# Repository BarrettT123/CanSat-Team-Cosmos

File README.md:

(The software I contributed to this project can be found in the CanSat-Team-Cosmos-Software repository)

Cansat Competition Description:
- The Cansat competition is a design-build-fly competition that provides teams with an
opportunity to experience the design life-cycle of an aerospace system. The Cansat
competition is designed to reflect a typical aerospace program on a small scale and includes
all aspects of an aerospace program from the preliminary design review to post flight review.
The mission and its requirements are designed to reflect various aspects of real world
missions including telemetry, communications, and autonomous operations. Each team is
scored throughout the competition on real-world deliverables such as schedules, design
review presentations, and demonstration flights.

Mission Overview:
- Design a Cansat that consists of a payload and a container that mounts on top of the rocket.
The payload rests inside the container at launch and includes the nose cone as part of the
payload.
- The container with the payload shall deploy from the rocket when the rocket reaches peak
altitude and the rocket motor ejection forces a separation. The container with the payload
shall descend at a rate of no more than 20 meters/second using a parachute that
automatically deploys at separation.
- At 75% peak altitude, the payload shall separate from the container and descend using an
auto-gyro descent control system until landing. The descent rate shall be 5 meters/second.
- A video camera shall show the separation of the payload from the container and the auto-gyro
functioning. A second video camera shall be pointing downward at 45 degrees from nadir
and oriented north during descent and be spin stabilized so that the view of the earth is not
rotating.
- The Cansat shall collect sensor data during ascent and descent and transmit the data to a
ground station at a 1 Hz rate. The sensor data shall include interior temperature, battery
voltage, altitude, auto-gyro rotation rate, acceleration, rate, magnetic field, and GPS position.

Post-Flight Cansat Payload:

Ground Station during Landing:

Software Contributors:
- `GCS`:
  - Diego Romero-Cardona

- `FSW`:
  - Caleb Wiley
  - Akhil Samiraju
  - Barrett Twining
  - Diego Romero-Cardona

- `PID Board`:
  - Caleb Wiley
  - Barrett Twining
  - Luke Wiggins

Competition Flight Data:
|TEAM_ID|MISSION_TIME|PACKET_COUNT|MODE|STATE        |ALTITUDE|TEMPERATURE|PRESSURE|VOLTAGE|GYRO_R |GYRO_P |GYRO_Y  |ACCEL_R|ACCEL_P|ACCEL_Y|MAG_R|MAG_P|MAG_Y|AUTO_GYRO_ROTATION_RATE|GPS_TIME|GPS_ALTITUDE|GPS_LATITUDE|GPS_LONGITUDE|GPS_SATS|CMD_ECHO   |TEAM_NAME|
|-------|------------|------------|----|-------------|--------|-----------|--------|-------|-------|-------|--------|-------|-------|-------|-----|-----|-----|-----------------------|--------|------------|------------|-------------|--------|-----------|---------|
|3195   |18:26:32    |972         |F   |LAUNCH_PAD   |-0.9    |40.6       |915.5   |7.9    |-0.79  |-1.28  |0.24    |-0.02  |0.00   |-0.49  |-42.6|-3.0 |61.6 |0                      |00:00:00|0.0         |0.00000     |0.00000      |0       |ST_UTC_TIME|COSMOS   |
|3195   |18:26:33    |973         |F   |LAUNCH_PAD   |-0.9    |40.7       |915.5   |7.9    |-0.67  |-0.98  |0.37    |-0.02  |-0.00  |-0.49  |-43.5|-2.9 |59.0 |0                      |00:00:00|0.0         |0.00000     |0.00000      |0       |ST_UTC_TIME|COSMOS   |
|3195   |18:26:38    |978         |F   |ASCENT       |186.3   |40.7       |895.4   |7.9    |-10.68 |7.63   |-123.54 |-0.10  |-0.05  |-4.00  |-45.7|-7.9 |61.9 |0                      |00:00:00|0.0         |0.00000     |0.00000      |0       |ST_UTC_TIME|COSMOS   |
|3195   |18:26:39    |979         |F   |ASCENT       |455.9   |40.6       |867.0   |7.9    |24.29  |-9.09  |-300.78 |-0.12  |0.09   |0.64   |-37.9|-2.8 |63.8 |0                      |00:00:00|0.0         |0.00000     |0.00000      |0       |ST_UTC_TIME|COSMOS   |
|3195   |18:26:40    |980         |F   |ASCENT       |478.8   |40.6       |864.7   |7.9    |3.36   |-19.84 |-251.46 |-0.04  |0.14   |0.51   |-33.1|-3.6 |62.0 |0                      |00:00:00|0.0         |0.00000     |0.00000      |0       |ST_UTC_TIME|COSMOS   |
|3195   |18:26:41    |981         |F   |APOGEE       |500.4   |40.6       |862.4   |7.9    |-1.53  |-13.43 |-183.53 |0.01   |0.15   |0.31   |-6.4 |-20.7|62.3 |0                      |00:00:00|0.0         |0.00000     |0.00000      |0       |ST_UTC_TIME|COSMOS   |
|3195   |18:26:42    |982         |F   |APOGEE       |530.2   |40.5       |859.3   |7.9    |8.67   |-17.94 |-138.37 |-0.02  |0.10   |0.20   |-46.8|-33.5|58.3 |0                      |00:00:00|0.0         |0.00000     |0.00000      |0       |ST_UTC_TIME|COSMOS   |
|3195   |18:26:43    |983         |F   |APOGEE       |557.5   |40.5       |856.5   |7.9    |5.19   |-14.28 |-94.97  |-0.02  |0.06   |0.12   |-5.4 |-31.5|58.2 |0                      |00:00:00|0.0         |0.00000     |0.00000      |0       |ST_UTC_TIME|COSMOS   |
|3195   |18:26:44    |984         |F   |APOGEE       |579.7   |40.5       |854.3   |7.9    |4.88   |-12.02 |-74.28  |-0.00  |0.03   |0.07   |-32.1|-4.0 |63.1 |0                      |00:00:00|0.0         |0.00000     |0.00000      |0       |ST_UTC_TIME|COSMOS   |
|3195   |18:26:45    |985         |F   |APOGEE       |597.4   |40.5       |852.4   |7.9    |1.59   |-8.97  |-56.64  |-0.00  |0.01   |0.03   |-49.3|-27.0|60.7 |0                      |00:00:00|0.0         |0.00000     |0.00000      |0       |ST_UTC_TIME|COSMOS   |
|3195   |18:26:46    |986         |F   |APOGEE       |611.3   |40.6       |851.0   |7.9    |-27.71 |-4.70  |-52.43  |-0.00  |-0.03  |0.05   |-36.9|-36.6|62.3 |0                      |00:00:00|0.0         |0.00000     |0.00000      |0       |ST_UTC_TIME|COSMOS   |
|3195   |18:26:47    |987         |F   |APOGEE       |616.2   |40.6       |850.5   |7.9    |23.19  |31.19  |-55.60  |0.01   |-0.02  |0.02   |-15.8|-34.8|61.7 |0                      |00:00:00|0.0         |0.00000     |0.00000      |0       |ST_UTC_TIME|COSMOS   |
|3195   |18:26:48    |988         |F   |DESCENT      |612.7   |40.6       |850.9   |7.9    |-62.93 |243.71 |-11.78  |0.20   |0.02   |-0.08  |9.2  |-9.7 |-12.0|0                      |00:00:00|0.0         |0.00000     |0.00000      |0       |ST_UTC_TIME|COSMOS   |
|3195   |18:26:49    |989         |F   |DESCENT      |603.2   |40.6       |851.9   |7.9    |-166.63|83.56  |115.36  |0.48   |-0.20  |0.09   |3.3  |-28.4|-22.3|0                      |00:00:00|0.0         |0.00000     |0.00000      |0       |ST_UTC_TIME|COSMOS   |
|3195   |18:26:51    |991         |F   |DESCENT      |569.9   |40.6       |855.3   |7.9    |355.41 |88.93  |179.75  |0.45   |0.10   |0.11   |-25.0|-19.3|-34.5|0                      |00:00:00|0.0         |0.00000     |0.00000      |0       |ST_UTC_TIME|COSMOS   |
|3195   |18:26:52    |992         |F   |DESCENT      |551.7   |40.6       |857.1   |7.9    |20.14  |78.74  |325.38  |-0.07  |0.31   |0.35   |-11.4|9.3  |-19.6|0                      |00:00:00|0.0         |0.00000     |0.00000      |0       |ST_UTC_TIME|COSMOS   |
|3195   |18:26:53    |993         |F   |DESCENT      |533.0   |40.6       |859.1   |7.9    |156.19 |229.92 |301.57  |-0.15  |0.42   |0.35   |-12.9|-13.2|-32.8|0                      |00:00:00|0.0         |0.00000     |0.00000      |0       |ST_UTC_TIME|COSMOS   |
|3195   |18:26:54    |994         |F   |DESCENT      |510.8   |40.6       |861.4   |7.9    |146.97 |25.39  |286.56  |0.38   |-0.23  |0.42   |2.1  |-38.5|-21.2|0                      |00:00:00|0.0         |0.00000     |0.00000      |0       |ST_UTC_TIME|COSMOS   |
|3195   |18:26:55    |995         |F   |DESCENT      |490.6   |40.6       |863.4   |7.9    |-86.98 |-158.63|330.69  |0.14   |0.61   |0.31   |-38.7|3.5  |-26.8|0                      |00:00:00|0.0         |0.00000     |0.00000      |0       |ST_UTC_TIME|COSMOS   |
|3195   |18:26:56    |996         |F   |DESCENT      |472.7   |40.6       |865.3   |7.8    |69.27  |195.80 |316.77  |0.37   |0.50   |0.32   |-36.7|3.0  |-26.7|0                      |00:00:00|0.0         |0.00000     |0.00000      |0       |ST_UTC_TIME|COSMOS   |
|3195   |18:26:57    |997         |F   |DESCENT      |451.3   |40.6       |867.5   |7.9    |134.70 |77.64  |407.17  |0.46   |0.32   |0.41   |6.7  |-10.9|-18.6|0                      |00:00:00|0.0         |0.00000     |0.00000      |0       |ST_UTC_TIME|COSMOS   |
|3195   |18:26:58    |998         |F   |DESCENT      |434.0   |40.6       |869.3   |7.9    |-62.81 |136.17 |393.92  |-0.05  |0.22   |0.41   |-57.7|-2.6 |-18.7|0                      |00:00:00|0.0         |0.00000     |0.00000      |0       |ST_UTC_TIME|COSMOS   |
|3195   |18:26:59    |999         |F   |DESCENT      |414.3   |40.6       |871.4   |7.9    |-250.37|206.73 |394.04  |-0.22  |0.51   |0.24   |-26.8|12.5 |-19.1|0                      |00:00:00|0.0         |0.00000     |0.00000      |0       |ST_UTC_TIME|COSMOS   |
|3195   |18:27:00    |1000        |F   |DESCENT      |396.6   |40.6       |873.2   |7.9    |-7.32  |90.88  |316.10  |-0.02  |0.25   |0.43   |-58.1|1.8  |-17.3|0                      |00:00:00|0.0         |0.00000     |0.00000      |0       |ST_UTC_TIME|COSMOS   |
|3195   |18:27:01    |1001        |F   |DESCENT      |379.0   |40.6       |875.1   |7.9    |-269.53|371.89 |410.64  |-0.24  |0.67   |-0.02  |-29.9|13.9 |-22.2|0                      |00:00:00|0.0         |0.00000     |0.00000      |0       |ST_UTC_TIME|COSMOS   |
|3195   |18:27:02    |1002        |F   |DESCENT      |358.8   |40.6       |877.2   |7.8    |-180.79|100.16 |443.54  |-0.40  |0.28   |0.37   |-53.6|6.0  |-18.8|0                      |00:00:00|0.0         |0.00000     |0.00000      |0       |ST_UTC_TIME|COSMOS   |
|3195   |18:27:03    |1003        |F   |PROBE_RELEASE|329.8   |40.4       |880.2   |7.9    |156.86 |-34.48 |512.76  |-0.11  |-0.04  |0.39   |-47.8|-4.9 |-23.5|0                      |00:00:00|0.0         |0.00000     |0.00000      |0       |ST_UTC_TIME|COSMOS   |
|3195   |18:27:04    |1004        |F   |PROBE_RELEASE|306.5   |39.8       |882.7   |7.8    |171.81 |-233.03|429.14  |0.25   |-0.46  |0.24   |-32.3|-46.6|-22.5|0                      |00:00:00|0.0         |0.00000     |0.00000      |0       |ST_UTC_TIME|COSMOS   |
|3195   |18:27:05    |1005        |F   |PROBE_RELEASE|290.9   |39.4       |884.3   |7.9    |195.19 |-323.36|325.81  |0.26   |-0.57  |0.16   |-14.8|-63.6|-2.6 |0                      |00:00:00|0.0         |0.00000     |0.00000      |0       |ST_UTC_TIME|COSMOS   |
|3195   |18:27:06    |1006        |F   |PROBE_RELEASE|275.7   |39.1       |885.9   |7.9    |205.02 |-142.40|310.79  |-0.13  |-0.16  |0.31   |-18.2|-9.4 |-30.4|0                      |00:00:00|0.0         |0.00000     |0.00000      |0       |ST_UTC_TIME|COSMOS   |
|3195   |18:27:07    |1007        |F   |PROBE_RELEASE|256.2   |38.6       |888.0   |7.9    |125.61 |-119.32|473.08  |0.42   |-0.12  |0.36   |-9.1 |-58.5|-6.7 |0                      |00:00:00|0.0         |0.00000     |0.00000      |0       |ST_UTC_TIME|COSMOS   |
|3195   |18:27:08    |1008        |F   |PROBE_RELEASE|238.0   |38.2       |889.9   |7.9    |191.59 |-214.36|288.39  |-0.32  |0.07   |0.37   |-22.8|-3.7 |-29.0|0                      |00:00:00|0.0         |0.00000     |0.00000      |0       |ST_UTC_TIME|COSMOS   |
|3195   |18:27:09    |1009        |F   |PROBE_RELEASE|219.2   |37.8       |891.9   |7.9    |147.58 |15.56  |386.84  |-0.06  |0.00   |0.43   |-22.3|-4.4 |-31.7|0                      |00:00:00|0.0         |0.00000     |0.00000      |0       |ST_UTC_TIME|COSMOS   |
|3195   |18:27:10    |1010        |F   |PROBE_RELEASE|200.3   |37.4       |893.9   |8.0    |131.29 |-99.98 |549.99  |-0.41  |-0.09  |0.40   |-50.2|5.7  |-20.6|0                      |00:00:00|0.0         |0.00000     |0.00000      |0       |ST_UTC_TIME|COSMOS   |
|3195   |18:27:11    |1011        |F   |PROBE_RELEASE|180.6   |37.2       |896.0   |8.0    |18.13  |-7.69  |472.23  |0.04   |0.21   |0.47   |-10.3|-10.8|-28.9|0                      |00:00:00|0.0         |0.00000     |0.00000      |0       |ST_UTC_TIME|COSMOS   |
|3195   |18:27:12    |1012        |F   |PROBE_RELEASE|160.5   |36.9       |898.2   |7.9    |-168.70|52.31  |724.73  |0.42   |0.11   |0.42   |-23.5|-25.8|-30.3|0                      |00:00:00|0.0         |0.00000     |0.00000      |0       |ST_UTC_TIME|COSMOS   |
|3195   |18:27:13    |1013        |F   |PROBE_RELEASE|147.7   |35.9       |899.5   |8.0    |-150.45|-159.18|79.22   |0.09   |-0.11  |0.46   |-1.4 |-33.5|-23.6|0                      |00:00:00|0.0         |0.00000     |0.00000      |0       |ST_UTC_TIME|COSMOS   |
|3195   |18:27:14    |1014        |F   |PROBE_RELEASE|138.8   |34.6       |900.5   |7.9    |137.51 |122.25 |-408.87 |-0.18  |0.10   |-0.44  |-75.2|-29.1|21.8 |0                      |00:00:00|0.0         |0.00000     |0.00000      |0       |ST_UTC_TIME|COSMOS   |
|3195   |18:27:15    |1015        |F   |PROBE_RELEASE|113.2   |33.8       |903.2   |7.9    |64.15  |-101.81|-1292.79|-0.10  |0.34   |-0.60  |-76.4|-3.2 |23.0 |0                      |00:00:00|0.0         |0.00000     |0.00000      |0       |ST_UTC_TIME|COSMOS   |
|3195   |18:27:16    |1016        |F   |PROBE_RELEASE|99.8    |33.1       |904.7   |7.9    |-15.20 |245.54 |-1796.75|0.48   |-0.07  |-0.98  |-22.2|-44.7|60.2 |0                      |00:00:00|0.0         |0.00000     |0.00000      |0       |ST_UTC_TIME|COSMOS   |
|3195   |18:27:17    |1017        |F   |PROBE_RELEASE|83.2    |32.7       |906.5   |7.9    |59.20  |8.79   |-1999.76|0.42   |0.18   |-0.61  |-7.2 |-42.0|57.1 |0                      |00:00:00|0.0         |0.00000     |0.00000      |0       |ST_UTC_TIME|COSMOS   |
|3195   |18:27:18    |1018        |F   |PROBE_RELEASE|72.7    |32.6       |907.6   |7.9    |28.56  |-3.36  |-1999.76|-0.06  |-0.16  |-0.48  |-5.2 |-23.6|60.7 |0                      |00:00:00|0.0         |0.00000     |0.00000      |0       |ST_UTC_TIME|COSMOS   |
|3195   |18:27:19    |1019        |F   |PROBE_RELEASE|63.5    |32.4       |908.6   |7.9    |33.87  |91.13  |-1999.76|-0.17  |0.33   |-0.62  |-6.9 |-12.3|61.6 |0                      |00:00:00|0.0         |0.00000     |0.00000      |0       |ST_UTC_TIME|COSMOS   |
|3195   |18:27:20    |1020        |F   |PROBE_RELEASE|54.1    |32.3       |909.6   |7.9    |79.65  |23.56  |-1999.76|0.05   |0.16   |-0.48  |4.5  |-7.5 |53.2 |0                      |00:00:00|0.0         |0.00000     |0.00000      |0       |ST_UTC_TIME|COSMOS   |
|3195   |18:27:21    |1021        |F   |PROBE_RELEASE|45.0    |32.1       |910.6   |7.8    |30.40  |82.82  |-1999.76|0.24   |0.05   |-0.56  |-23.2|-16.7|68.2 |0                      |00:00:00|0.0         |0.00000     |0.00000      |0       |ST_UTC_TIME|COSMOS   |
|3195   |18:27:22    |1022        |F   |PROBE_RELEASE|35.6    |32.0       |911.6   |7.9    |-2.08  |62.38  |-1999.76|0.10   |0.08   |-0.49  |-63.0|-12.4|55.5 |0                      |00:00:00|0.0         |0.00000     |0.00000      |0       |ST_UTC_TIME|COSMOS   |
|3195   |18:27:23    |1023        |F   |PROBE_RELEASE|26.1    |31.9       |912.6   |7.8    |40.34  |34.42  |-1999.76|0.10   |0.09   |-0.43  |-22.2|-6.5 |66.8 |0                      |00:00:00|0.0         |0.00000     |0.00000      |0       |ST_UTC_TIME|COSMOS   |
|3195   |18:27:24    |1024        |F   |PROBE_RELEASE|16.4    |31.8       |913.7   |7.9    |15.26  |23.68  |-1999.76|0.26   |0.17   |-0.56  |-54.9|-31.0|57.9 |0                      |00:00:00|0.0         |0.00000     |0.00000      |0       |ST_UTC_TIME|COSMOS   |
|3195   |18:27:25    |1025        |F   |PROBE_RELEASE|8.5     |31.3       |914.5   |7.8    |16.97  |-82.09 |181.58  |-0.06  |-0.02  |-0.12  |-76.6|-21.8|29.5 |0                      |00:00:00|0.0         |0.00000     |0.00000      |0       |ST_UTC_TIME|COSMOS   |
|3195   |18:27:26    |1026        |F   |PROBE_RELEASE|8.3     |31.5       |914.6   |7.9    |3.85   |2.87   |-1.89   |-0.33  |-0.01  |-0.37  |-74.8|-20.1|41.1 |0                      |00:00:00|0.0         |0.00000     |0.00000      |0       |PARTY_ON   |COSMOS   |
|3195   |18:27:28    |1028        |F   |LANDED       |8.1     |31.6       |914.6   |7.9    |-0.67  |0.18   |0.79    |-0.32  |-0.02  |-0.37  |-74.7|-20.5|40.0 |0                      |00:00:00|0.0         |0.00000     |0.00000      |0       |PARTY_ON   |COSMOS   |
|3195   |18:27:29    |1029        |F   |LANDED       |8.0     |31.7       |914.6   |7.9    |1.04   |-0.79  |-0.67   |-0.33  |-0.01  |-0.37  |-73.7|-21.4|37.4 |0                      |00:00:00|0.0         |0.00000     |0.00000      |0       |PARTY_ON   |COSMOS   |
|3195   |18:27:30    |1030        |F   |LANDED       |7.9     |31.8       |914.6   |7.9    |-0.37  |1.65   |0.00    |-0.33  |-0.01  |-0.37  |-72.8|-20.6|41.2 |0                      |00:00:00|0.0         |0.00000     |0.00000      |0       |PARTY_ON   |COSMOS   |
|3195   |18:27:31    |1031        |F   |LANDED       |7.8     |31.9       |914.6   |7.9    |0.12   |1.46   |0.79    |-0.32  |-0.01  |-0.37  |-73.8|-20.1|41.4 |0                      |00:00:00|0.0         |0.00000     |0.00000      |0       |PARTY_ON   |COSMOS   |

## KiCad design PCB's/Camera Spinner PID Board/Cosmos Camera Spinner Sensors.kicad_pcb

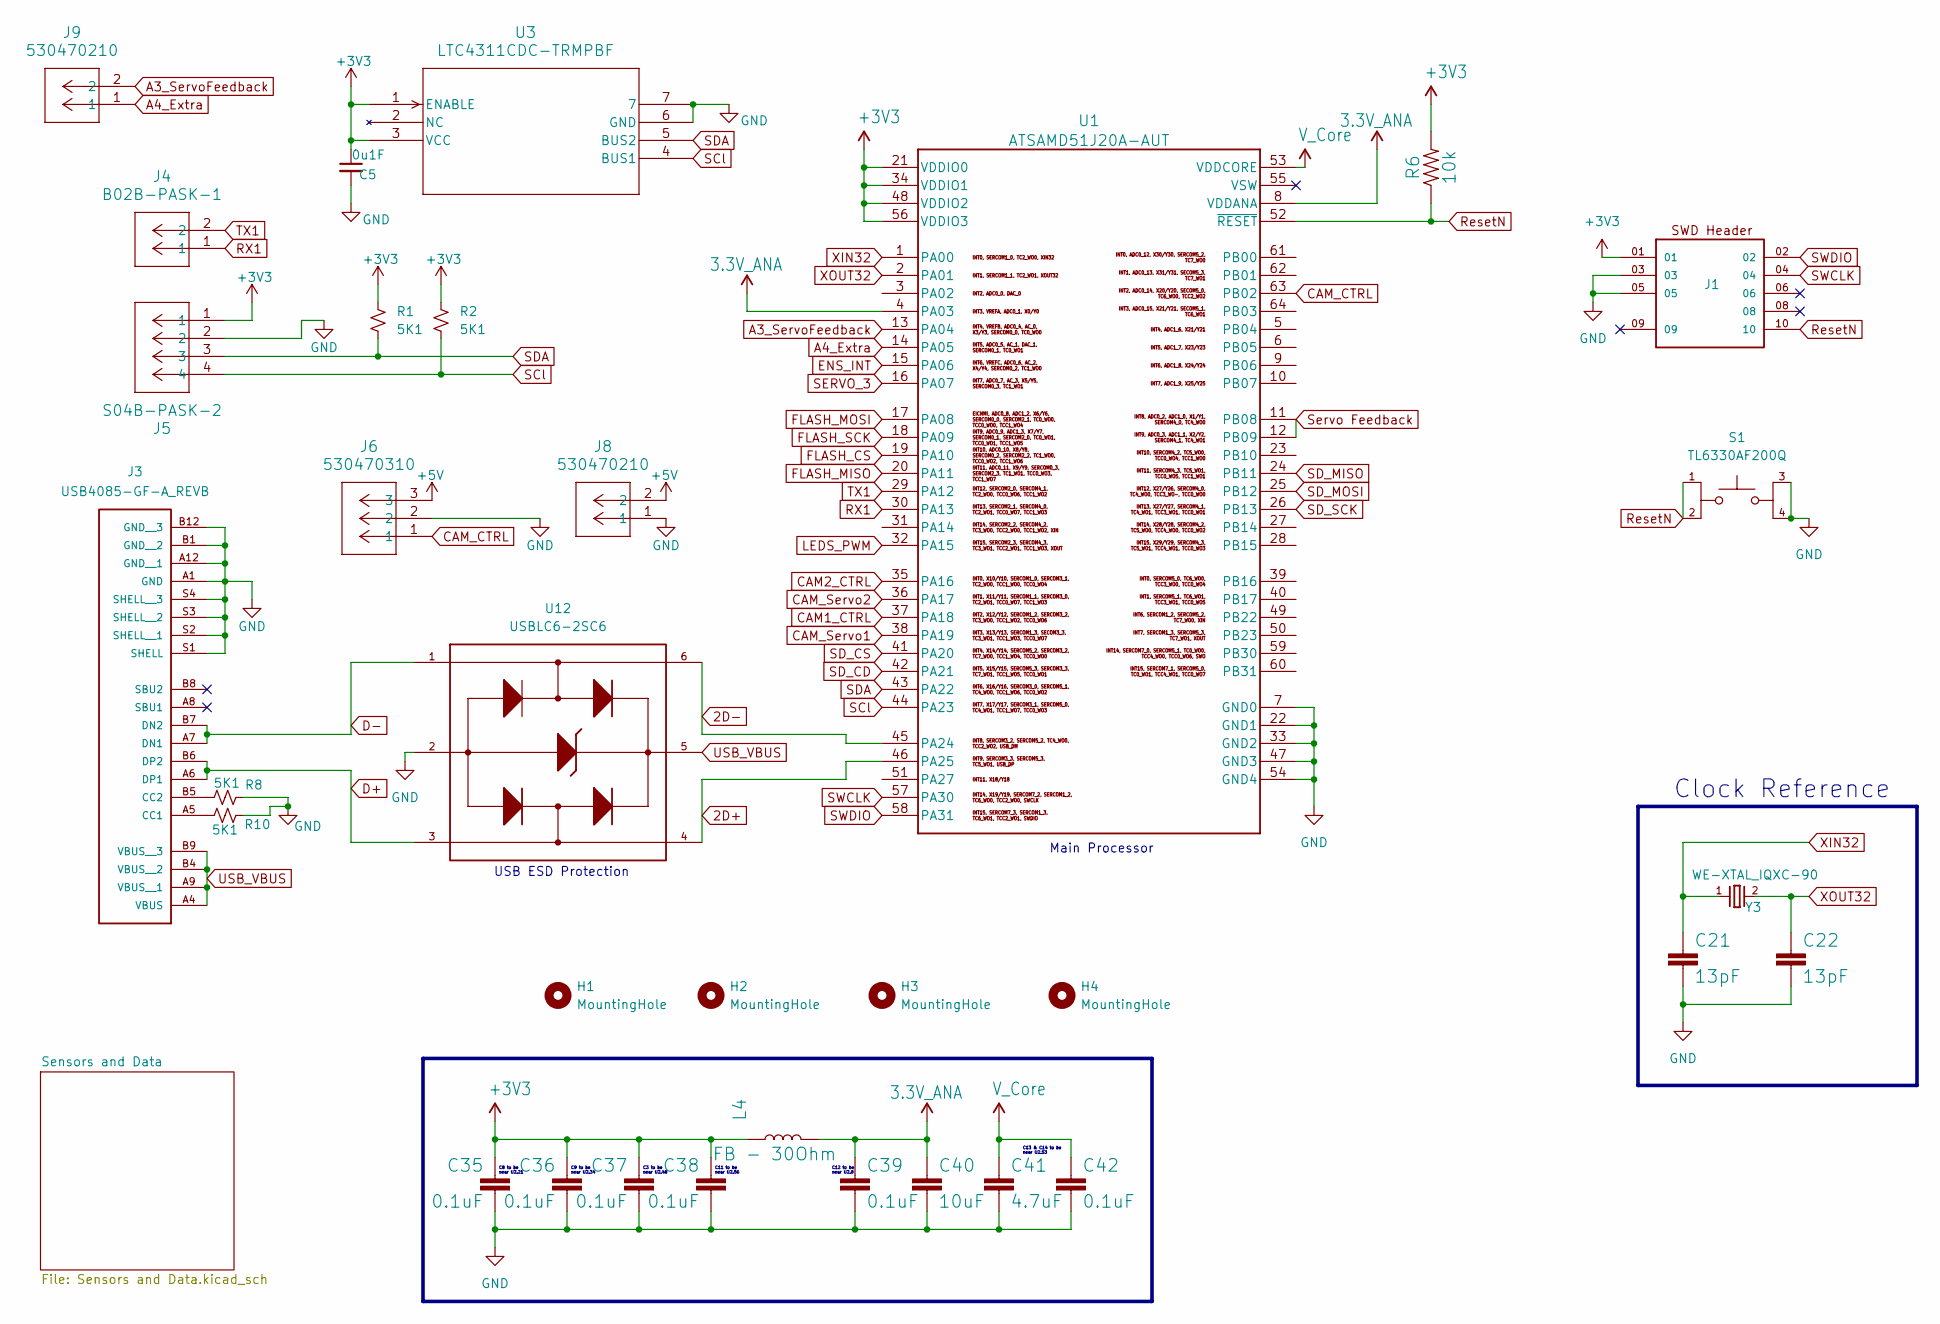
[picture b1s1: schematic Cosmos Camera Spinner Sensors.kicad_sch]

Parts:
C5: 0u1F; C_0603_1608Metric
C21, C22: 13pF; C_0603_1608Metric
C35, C36, C37, C38, C39, C42: 0.1uF; C_0603_1608Metric
C40: 10uF; C_0603_1608Metric
C41: 4.7uF; C_0603_1608Metric
H1, H2, H3, H4: MountingHole; MountingHole_2.2mm_M2_ISO14580
J1: FTSH-105-X-X-DV-007-P-X; SAMTEC_FTSH-105-X-X-DV-007-P-X
J3: USB4085-GF-A_REVB; GCT_USB4085-GF-A_REVB
J4: B02B-PASK-1; CONN02_530470210_MOL
J5: S04B-PASK-2; CONN4_S04B-PASK_JST
J6: 530470310; CONN03_530470310_MOL
J8, J9: 530470210; CONN02_530470210_MOL
L4: FB - 30Ohm; R_0603_1608Metric
R1, R2, R8, R10: 5K1; R_0603_1608Metric
R6: 10k; R_0603_1608Metric
S1: TL6330AF200Q; SW_TL6330AF200Q
U1: ATSAMD51J20A-AUT; QFN64_9x9MC_MCH_SAMD51J20A_MUT
U3: LTC4311CDC-TRMPBF; DFN-6_DC_LIT
U12: USBLC6-2SC6; USBLC_6
Y3: WE-XTAL_IQXC-90

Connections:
2D+: U1.46 (PA25), U12.4
2D-: U1.45 (PA24), U12.6
3.3V_ANA: C39.1, C40.1, L4.2, U1.4 (PA03), U1.8 (VDDANA)
+3V3: C5.1, C35.1, C36.1, C37.1, C38.1, J1.01, J5.1, L4.1, R1.1, R2.1, R6.2, U1.21 (VDDIO0), U1.34 (VDDIO1), U1.48 (VDDIO2), U1.56 (VDDIO3), U3.1 (ENABLE), U3.3 (VCC); also elsewhere on the board
+5V: J6.3, J8.2
A3_ServoFeedback: J9.2, U1.13 (PA04)
A4_Extra: J9.1, U1.14 (PA05)
CAM1_CTRL: U1.37 (PA18)
CAM2_CTRL: U1.35 (PA16)
CAM_CTRL: J6.1, U1.63 (PB02)
CAM_Servo1: U1.38 (PA19)
CAM_Servo2: U1.36 (PA17)
D+: J3.A6 (DP1), J3.B6 (DP2), U12.3
D-: J3.A7 (DN1), J3.B7 (DN2), U12.1
ENS_INT: U1.15 (PA06); also elsewhere on the board
FLASH_CS: U1.19 (PA10); also elsewhere on the board
FLASH_MISO: U1.20 (PA11); also elsewhere on the board
FLASH_MOSI: U1.17 (PA08); also elsewhere on the board
FLASH_SCK: U1.18 (PA09); also elsewhere on the board
GND: C5.2, C21.2, C22.2, C35.2, C36.2, C37.2, C38.2, C39.2, C40.2, C41.2, C42.2, J1.03, J1.05, J3.A1 (GND), J3.A12 (GND__1), J3.B1 (GND__2), J3.B12 (GND__3), J3.S1 (SHELL), J3.S2 (SHELL__1), J3.S3 (SHELL__2), J3.S4 (SHELL__3), J5.2, J6.2, J8.1, R8.2, R10.2, S1.3, S1.4, U1.7 (GND0), U1.22 (GND1), U1.33 (GND2), U1.47 (GND3), U1.54 (GND4), U1.65, U3.6 (GND), U3.7, U12.2; also elsewhere on the board
LEDS_PWM: U1.32 (PA15)
unnamed: J3.A5 (CC1), R10.1
unnamed: J3.B5 (CC2), R8.1
RX1: J4.1, U1.30 (PA13)
ResetN: J1.10, R6.1, S1.1, S1.2, U1.52 (~RESET)
SCl: J5.4, R2.2, U1.44 (PA23), U3.4 (BUS1); also elsewhere on the board
SDA: J5.3, R1.2, U1.43 (PA22), U3.5 (BUS2); also elsewhere on the board
SD_CD: U1.42 (PA21); also elsewhere on the board
SD_CS: U1.41 (PA20); also elsewhere on the board
SD_MISO: U1.24 (PB11); also elsewhere on the board
SD_MOSI: U1.25 (PB12); also elsewhere on the board
SD_SCK: U1.26 (PB13); also elsewhere on the board
SERVO_3: U1.16 (PA07)
SWCLK: J1.04, U1.57 (PA30)
SWDIO: J1.02, U1.58 (PA31)
Servo Feedback: U1.11 (PB08), U1.12 (PB09)
TX1: J4.2, U1.29 (PA12)
USB_VBUS: J3.A4 (VBUS), J3.A9 (VBUS__1), J3.B4 (VBUS__2), J3.B9 (VBUS__3), U12.5
V_Core: C41.1, C42.1, U1.53 (VDDCORE)
XIN32: C21.1, U1.1 (PA00), Y3.1
XOUT32: C22.1, U1.2 (PA01), Y3.2

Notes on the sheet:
C12 to be near U2.8
C11 to be near U2.56
C13 & C14 to be near U2.53
USB ESD Protection
C9 to be near U2.34
C3 to be near U2.48
Clock Reference
C8 to be near U2.21
Main Processor

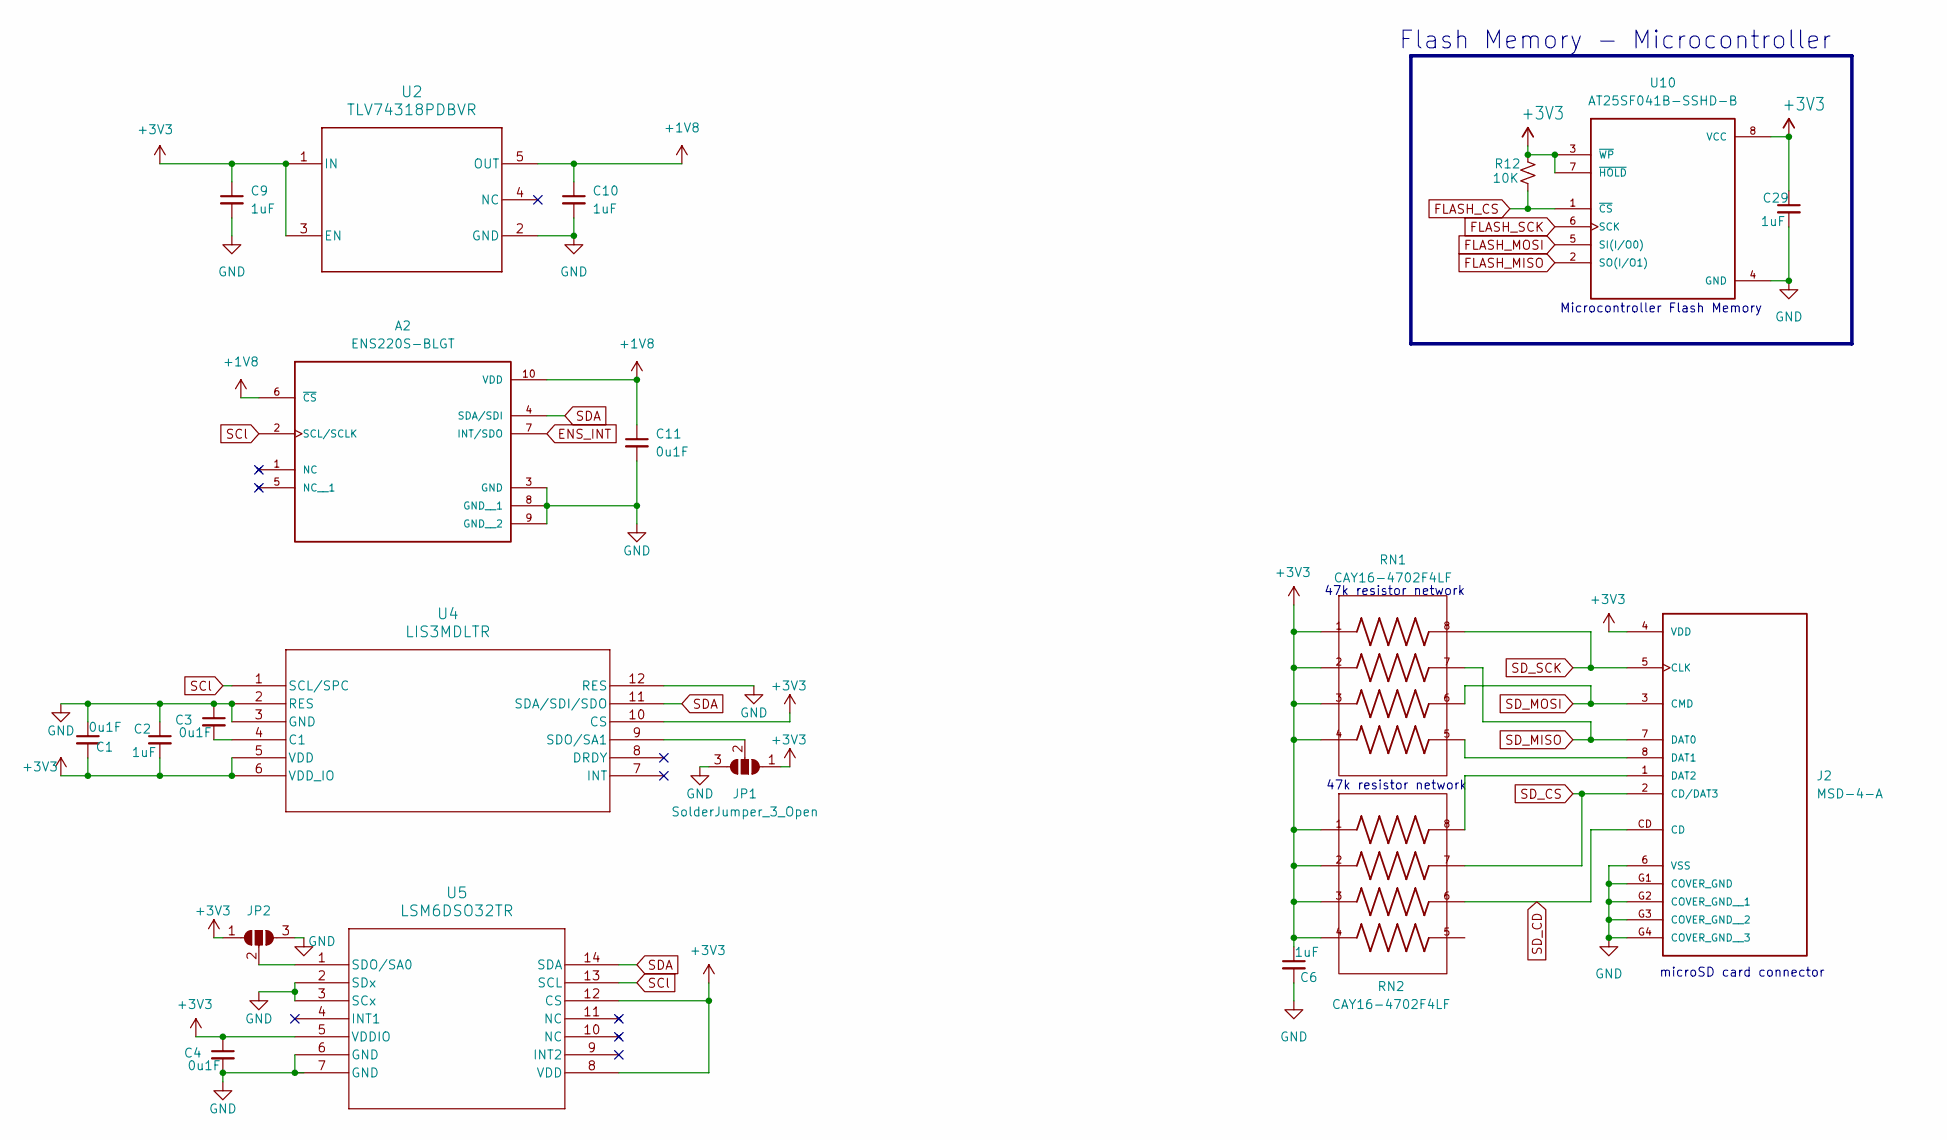
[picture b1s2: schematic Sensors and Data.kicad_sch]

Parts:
A2: ENS220S-BLGT; XDCR_ENS220S-BLGT
C1, C3, C4, C11: 0u1F; C_0603_1608Metric
C2, C6, C9, C10, C29: 1uF; C_0603_1608Metric
J2: MSD-4-A; CUI_MSD-4-A
JP1, JP2: SolderJumper_3_Open; SolderJumper-3_P1.3mm_Open_RoundedPad1.0x1.5mm
R12: 10K; R_0603_1608Metric
RN1, RN2: CAY16-4702F4LF; CAY16_4702F4LF
U2: TLV74318PDBVR
U4: LIS3MDLTR
U5: LSM6DSO32TR; LSM6DSO
U10: AT25SF041B-SSHD-B; AT25SF041B; PARTREV G

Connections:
+1V8: A2.6 (~CS), A2.10 (VDD), C10.1, C11.1, U2.5 (OUT)
+3V3: C1.2, C2.2, C4.1, C6.1, C9.1, C29.1, J2.4 (VDD), JP1.1 (A), JP2.1 (A), R12.1, RN1.1, RN1.2, RN1.3, RN1.4, RN2.1, RN2.2, RN2.3, RN2.4, U2.1 (IN), U2.3 (EN), U4.5 (VDD), U4.6 (VDD_IO), U4.10 (CS), U5.5 (VDDIO), U5.8 (VDD), U5.12 (CS), U10.3 (~WP), U10.7 (~HOLD), U10.8 (VCC); also elsewhere on the board
ENS_INT: A2.7 (INT/SDO); also elsewhere on the board
FLASH_CS: R12.2, U10.1 (~CS); also elsewhere on the board
FLASH_MISO: U10.2 (SO(I/O1)); also elsewhere on the board
FLASH_MOSI: U10.5 (SI(I/O0)); also elsewhere on the board
FLASH_SCK: U10.6 (SCK); also elsewhere on the board
GND: A2.3 (GND), A2.8 (GND__1), A2.9 (GND__2), C1.1, C2.1, C3.1, C4.2, C6.2, C9.2, C10.2, C11.2, C29.2, J2.6 (VSS), J2.G1 (COVER_GND), J2.G2 (COVER_GND__1), J2.G3 (COVER_GND__2), J2.G4 (COVER_GND__3), JP1.3 (B), JP2.3 (B), U2.2 (GND), U4.2 (RES), U4.3 (GND), U4.12 (RES), U5.2 (SDx), U5.3 (SCx), U5.6 (GND), U5.7 (GND), U10.4 (GND); also elsewhere on the board
unnamed: J2.8 (DAT1), RN1.5
unnamed: J2.1 (DAT2), RN2.8
unnamed: JP1.2 (C), U4.9 (SDO/SA1)
unnamed: JP2.2 (C), U5.1 (SDO/SA0)
unnamed: C3.2, U4.4 (C1)
SCl: A2.2 (SCL/SCLK), U4.1 (SCL/SPC), U5.13 (SCL); also elsewhere on the board
SDA: A2.4 (SDA/SDI), U4.11 (SDA/SDI/SDO), U5.14 (SDA); also elsewhere on the board
SD_CD: J2.CD, RN2.6; also elsewhere on the board
SD_CS: J2.2 (CD/DAT3), RN2.7; also elsewhere on the board
SD_MISO: J2.7 (DAT0), RN1.7; also elsewhere on the board
SD_MOSI: J2.3 (CMD), RN1.6; also elsewhere on the board
SD_SCK: J2.5 (CLK), RN1.8; also elsewhere on the board

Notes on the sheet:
Microcontroller Flash Memory
47k resistor network
microSD card connector
Flash Memory - Microcontroller

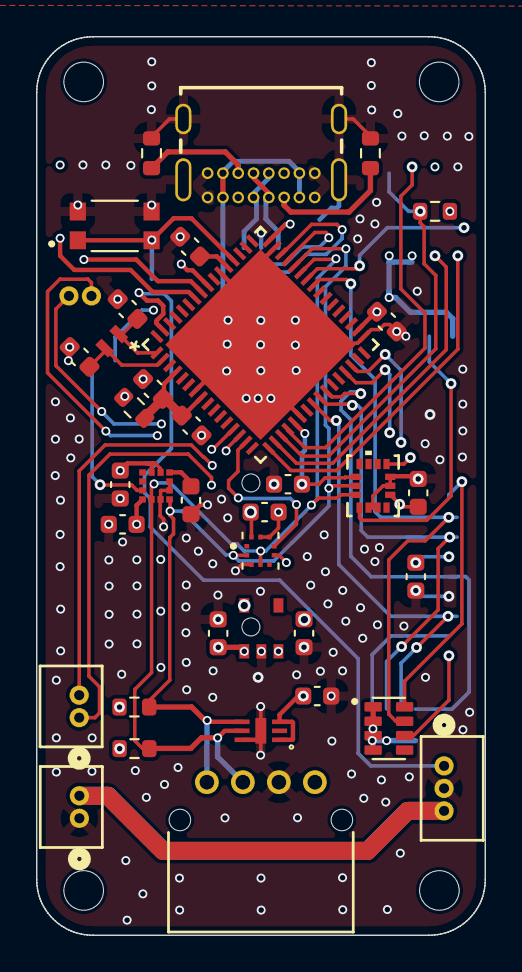
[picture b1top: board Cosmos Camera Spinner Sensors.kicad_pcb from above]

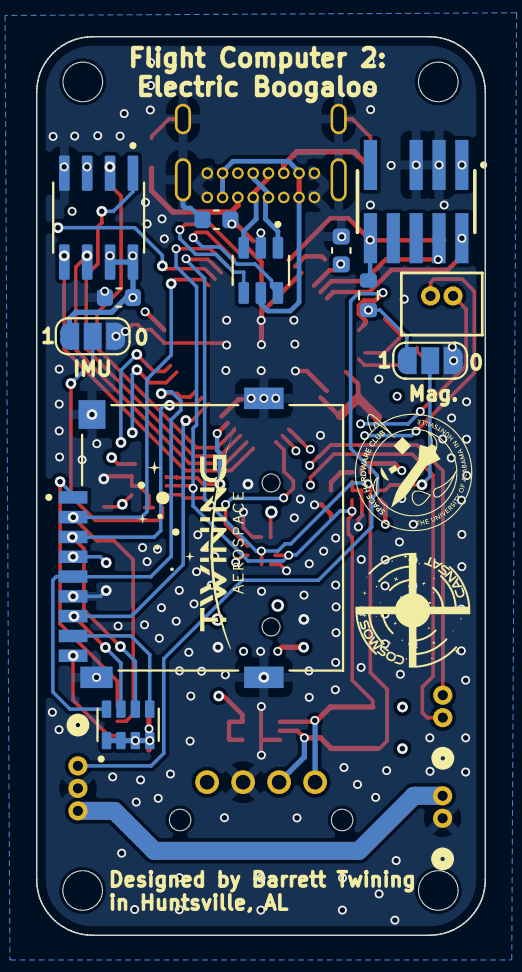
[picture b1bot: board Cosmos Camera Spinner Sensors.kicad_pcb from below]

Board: 4 copper layers, 24.9 x 49.9 mm, 52 parts (12 on the bottom side), 41 nets.

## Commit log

2025-06-18 Flight Computer design files
